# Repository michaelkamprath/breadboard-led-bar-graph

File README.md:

# Breadboard LED Bar Graphs

This repository contains some KiCad projects that implement LED bar graphs made out of discrete, rectangular LEDs and designed to minimize the footprint taken on a breadboard. This is done by making the connection to the breadboard being a single row of pin headers with one pin for each LED and one pin for ground, thus making these "common cathode" LEDs. However, nothing prevents the building from inserting the LEDs in reverse and thus making these bard graphs "common anode". Current limiting resistors are added by using resistor arrays.

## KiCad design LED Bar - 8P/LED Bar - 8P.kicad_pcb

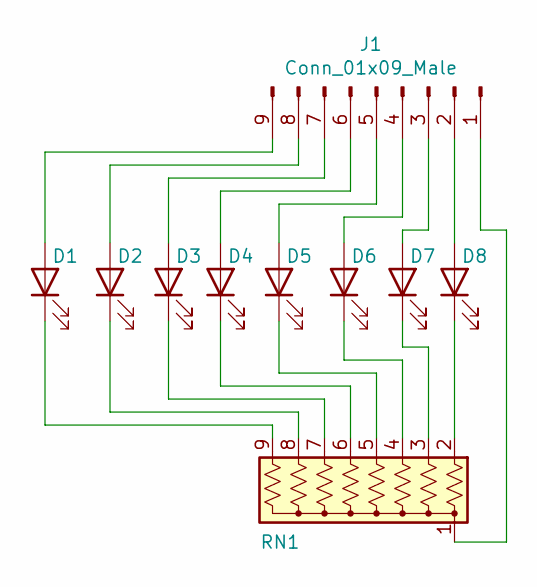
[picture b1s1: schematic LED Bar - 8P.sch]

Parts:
D1, D2, D3, D4, D5, D6, D7, D8: LED; LED_Rectangular_W5.0mm_H2.0mm
J1: Conn_01x09_Male; PinHeader_1x09_P2.54mm_Vertical
RN1: R_Network08_US; R_Array_SIP9

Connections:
unnamed: D1.1 (K), RN1.9 (R8)
unnamed: D1.2 (A), J1.9
unnamed: D2.1 (K), RN1.8 (R7)
unnamed: D2.2 (A), J1.8
unnamed: D3.1 (K), RN1.7 (R6)
unnamed: D3.2 (A), J1.7
unnamed: D4.1 (K), RN1.6 (R5)
unnamed: D4.2 (A), J1.6
unnamed: D5.1 (K), RN1.5 (R4)
unnamed: D5.2 (A), J1.5
unnamed: D6.1 (K), RN1.4 (R3)
unnamed: D6.2 (A), J1.4
unnamed: D7.1 (K), RN1.3 (R2)
unnamed: D7.2 (A), J1.3
unnamed: D8.1 (K), RN1.2 (R1)
unnamed: D8.2 (A), J1.2
unnamed: J1.1, RN1.1 (common)

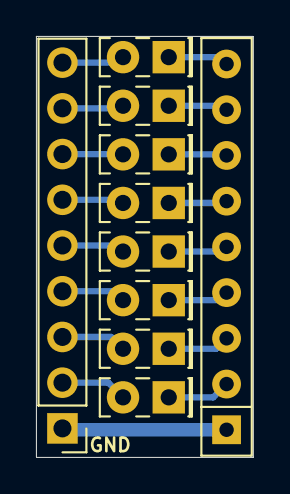
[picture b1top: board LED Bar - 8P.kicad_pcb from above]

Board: 2 copper layers, 12.0 x 23.4 mm, 10 parts (0 on the bottom side), 17 nets.

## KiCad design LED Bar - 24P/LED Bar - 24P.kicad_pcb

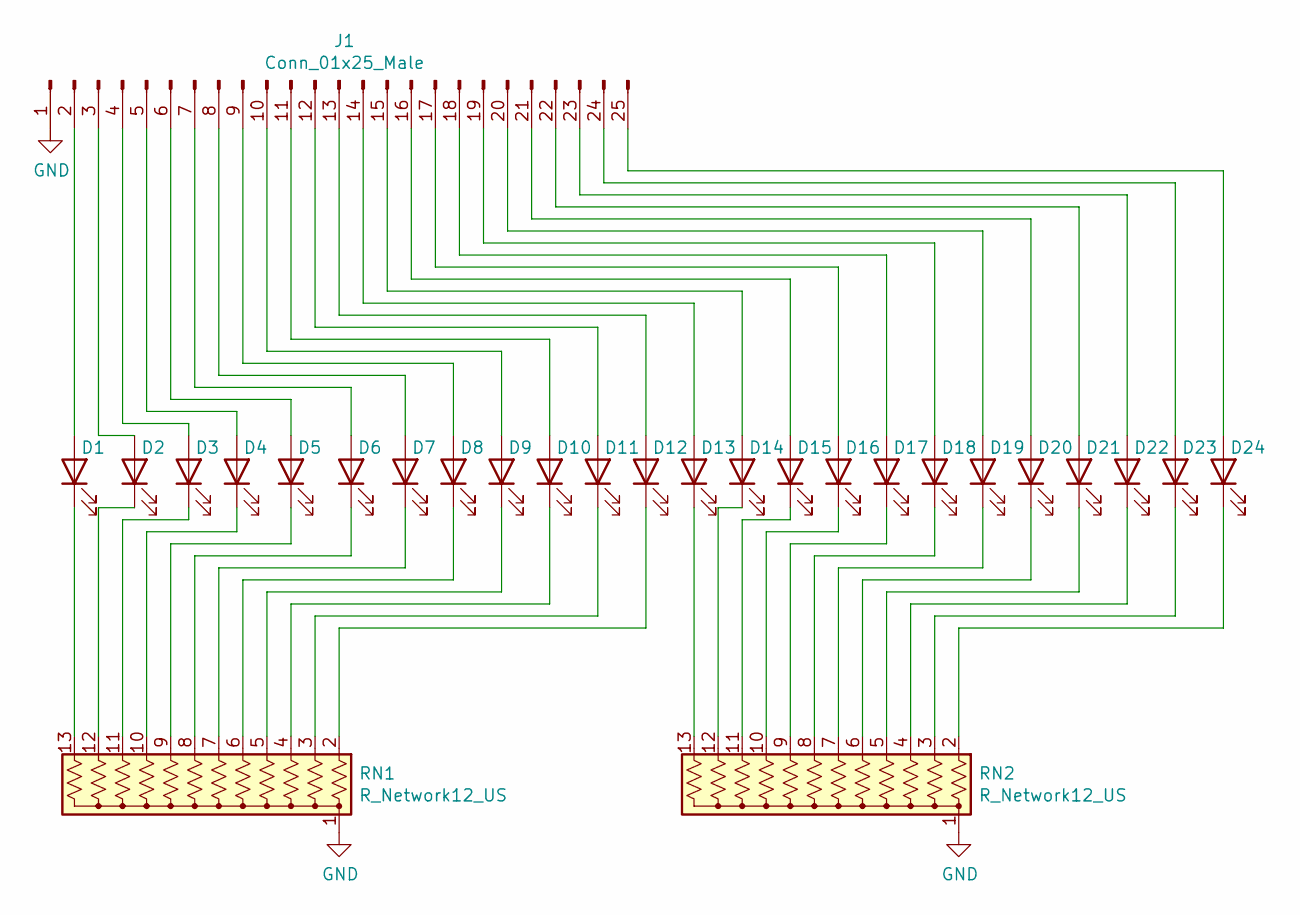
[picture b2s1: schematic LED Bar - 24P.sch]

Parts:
D1, D2, D3, D4, D5, D6, D7, D8, D9, D10, D11, D12, D13, D14, D15, D16, D17, D18, D19, D20, D21, D22, D23, D24: LED; LED_Rectangular_W5.0mm_H2.0mm
J1: Conn_01x25_Male; PinHeader_1x25_P2.54mm_Vertical
RN1, RN2: R_Network12_US; R_Array_SIP13

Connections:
GND: J1.1, RN1.1 (common), RN2.1 (common)
unnamed: D1.1 (K), RN1.13 (R12)
unnamed: D1.2 (A), J1.2
unnamed: D2.1 (K), RN1.12 (R11)
unnamed: D2.2 (A), J1.3
unnamed: D3.1 (K), RN1.11 (R10)
unnamed: D3.2 (A), J1.4
unnamed: D4.1 (K), RN1.10 (R9)
unnamed: D4.2 (A), J1.5
unnamed: D5.1 (K), RN1.9 (R8)
unnamed: D5.2 (A), J1.6
unnamed: D6.1 (K), RN1.8 (R7)
unnamed: D6.2 (A), J1.7
unnamed: D7.1 (K), RN1.7 (R6)
unnamed: D7.2 (A), J1.8
unnamed: D8.1 (K), RN1.6 (R5)
unnamed: D8.2 (A), J1.9
unnamed: D9.1 (K), RN1.5 (R4)
unnamed: D9.2 (A), J1.10
unnamed: D10.1 (K), RN1.4 (R3)
unnamed: D10.2 (A), J1.11
unnamed: D11.1 (K), RN1.3 (R2)
unnamed: D11.2 (A), J1.12
unnamed: D12.1 (K), RN1.2 (R1)
unnamed: D12.2 (A), J1.13
unnamed: D13.1 (K), RN2.13 (R12)
unnamed: D13.2 (A), J1.14
unnamed: D14.1 (K), RN2.12 (R11)
unnamed: D14.2 (A), J1.15
unnamed: D15.1 (K), RN2.11 (R10)
unnamed: D15.2 (A), J1.16
unnamed: D16.1 (K), RN2.10 (R9)
unnamed: D16.2 (A), J1.17
unnamed: D17.1 (K), RN2.9 (R8)
unnamed: D17.2 (A), J1.18
unnamed: D18.1 (K), RN2.8 (R7)
unnamed: D18.2 (A), J1.19
unnamed: D19.1 (K), RN2.7 (R6)
unnamed: D19.2 (A), J1.20
unnamed: D20.1 (K), RN2.6 (R5)
unnamed: D20.2 (A), J1.21
unnamed: D21.1 (K), RN2.5 (R4)
unnamed: D21.2 (A), J1.22
unnamed: D22.1 (K), RN2.4 (R3)
unnamed: D22.2 (A), J1.23
unnamed: D23.1 (K), RN2.3 (R2)
unnamed: D23.2 (A), J1.24
unnamed: D24.1 (K), RN2.2 (R1)
unnamed: D24.2 (A), J1.25

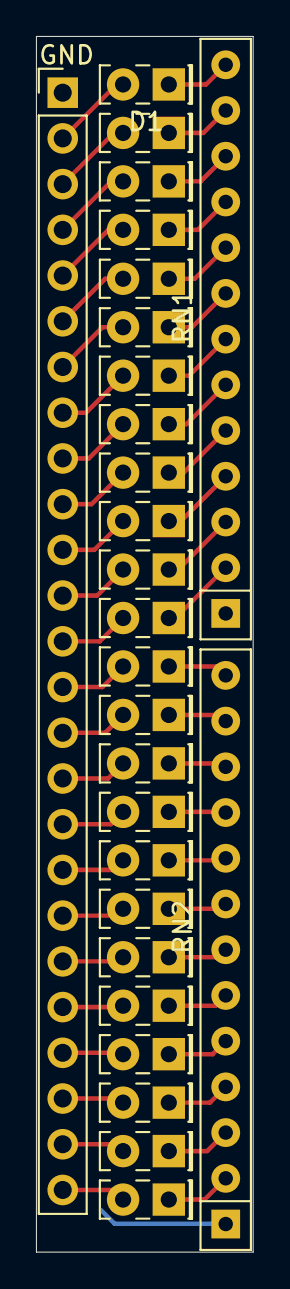
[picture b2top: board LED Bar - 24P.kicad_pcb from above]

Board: 2 copper layers, 12.0 x 67.5 mm, 27 parts (0 on the bottom side), 49 nets.

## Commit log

2021-09-20 added README
